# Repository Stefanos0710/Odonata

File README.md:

# Odonata

Odonata is an autonomous indoor drone controlled over a local network. I had the idea for the project, after I once bought a drone that broke after just two days because I struggled to control it manually. Sothat it doesn´t crash again, I decided to build a new,  autonomous drone and named it Odonata, after the Latin word for dragonfly.

The drone weighs about 300g and uses a 3S 11.1V 850mAh battery, giving it a flight time of roughly 5 minutes. With around 1100g of thrust, it achieves a 3:1 thrust-to-weight ratio, which allows precise flights. For navigation, it has 4 ToF (Time-of-Flight) sensors to track its position in the room, and it can perform controlled autonomous landings using a camera that detects AprilTags on the landing station. The landing station is designed with self-centering sticks, sothat even with a positioning error of about 1cm, the drone can still lands safely.

Odonata runs on a Raspberry Pi Zero 2W and a DarwinFPV flight controller, connected together via a custom PCB. With this setup the Pi can send and receive data using MAVLink commands (such as starting the motors, pitching, etc.). The project is split into two parts: the drone itself and a local server. The server hosts a web-based cockpit where you can monitor the drone, test the motors, and start-stop flights. Because it works locally, you can easily host the server on your laptop, PC, or a separate Raspberry Pi.

## First Flight

The first version of Odonata in flight:

[Watch in full quality on YouTube](https://www.youtube.com/shorts/tDMgUdCkJ7U)

## Zine Poster

Here is the Zine poster of my project Odonata:

## Website/Cockpit

Here you can see the user interface of the cockpit where you can monitor the drone and send commands:

## CAD Model

The CAD design of Odonata is split into several parts, like the arms, the walls, the base, the cover, and the propguards. Everything is attached using M2 screws and heat inserts, or slide-ins and snap-fits. The .step, .stl and f3d/f3z files can be found at the /CAD directory. Here are some nice renders of the assembled drone:

(All parts were modeled and rendered in Autodesk Fusion 360)

<details>
<summary><b>Click here to view more renders</b></summary>

</details>

## PCB

This custom PCB is designed in KiCad and makes the flawless communication between the Flight Controller and the Raspberry Pi Zero 2W possible, and also connects the servo, the ToF sensors and camera to a working system. It uses a 4-layer design for the optimal routing and to ensure no noise on the power lines.

### Schematics

### PCB-Layers

The PCB uses 4 layers: 1. TOP-Signal layer 2. GND layer 3. Power layer 4. Signal and GND layer

#### **1. Layer (Top-Signal)**

#### **2. Layer (GND)**

#### **3. Layer (Power)**

#### **4. Layer (Signal/GND)**

#### **PCB 3D-Rendering**

| Front | Back |
|----------|-------------|
|  |  |

#### JLCPCB Order

## How to build Odonata (Step-by-Step)

If you want to rebuild this drone without any modifications, you can follow these next steps. If you want to modify the drone, you can follow along the guide, you just have to adjust it to your changes:

### 1. Getting the parts

1. Download the whole repository on your computer by running these commands in your terminal to download the firmware, CAD, and PCB:

   ```bash
   git clone https://github.com/Stefanos0710/Odonata.git
   cd Odonata
   ```

   After that, you will have cloned the entire project onto your computer.

2. Next, you have to print out the 3D parts, and therefore you have 2 options, based on whether you have a 3D printer or not:
   1. If you have a 3D printer: upload the stl files from `/CAD/f3d_stl` into your slicer software. You have to print every file separately. So for the propguards you need 4, the motor arms you need 4, the base you need 1, the wall you need 1, the cover you need 1, and you need the camera holder. For the landing station, you need the catcher and the AprilTag holder.
   2. If you don't have a 3D printer, you can use a company like PCBWay, JLCPCB, or any other 3D printing service. There you have to upload the exact same files I mentioned previously and order them.
   3. Overall for the filament, if you can choose which one you can use, I would assume to use TPU for the propguards and print the rest with PETG for the best stability. For the color, if you like the style of the drone, it should be light/lime green and purple/blue.

3. Next, you should order the PCB. Therefore you need the gerber files which you find at `PCB/gerbers` as a `gerbers.zip` file. This file you can upload on a service like PCBWay, JLCPCB, or any other of your choice. Make sure to select 4 layers, and for the color it doesn't matter, but in this case I used the typical green one. Otherwise, I use the default options, so FR-4 as material.

4. Next, we need to get/buy the rest of the parts. A list with all parts you can find further down in the README, or in the `BOM.csv` file. There is the cost of the parts, the links, name, and description. INFO: the shipping cost is calculated for ordering to Bavaria, Germany, so it might change for you. But the rough price without shipping is 222,71€.

### 2. Setting up the Raspberry Pi Zero 2 W

After you got all the parts, we can start building the drone. And therefore we will start setting up the Raspberry Pi Zero 2 W:

1. Firstly, you need to download the Raspberry Pi Imager software on your computer, so that you can install the OS on the Raspberry Pi. First open this site https://www.raspberrypi.com/software/ and download it for your OS (Windows/macOS/Linux).
2. After downloading, you need to attach a micro SD card with at least 16GB to the computer, so that you can flash the OS and attach it later into the Raspberry Pi.
3. Then you choose the Raspberry Pi OS Lite, without the desktop, so that we don't waste resource power on that.
4. During that procedure, you will need to add the name (I assume to use "odonata" as the name), the WLAN (this must match the WLAN that you are connected to with your computer and later your server), and very important is to activate SSH, and lastly, you have to add a username and a password.
5. Then you detach the micro SD from your computer and attach it into the Raspberry Pi and connect it with a USB for power.
6. After waiting for about 5 min so that the OS can boot, you can type (for Windows):

   ```bash
   ssh yourusername@odonata.local
   ```

   And so you should be connected to the Raspberry Pi.
7. Now we update the system by typing in:

   ```bash
   sudo apt update
   sudo apt upgrade -y
   ```

8. After that, type in `sudo raspi-config` and activate the camera, the SPI, and the I2C.
9. After that, we have to install Python and Git. It's mostly already installed, but to update it's good:

   ```bash
   sudo apt install python3 python3-pip python3-venv git -y
   python3 --version
   pip3 --version
   git --version
   ```

   If you see no error, then everything is fine and installed.
10. And lastly, you have to copy the drone folder from firmware to the Raspberry Pi, and you can do it with this:

   ```bash
   git clone --depth 1 https://github.com/Stefanos0710/Odonata.git temp_repo
   mv temp_repo/firmware/drone ./drone
   mv temp_repo/firmware/requirements.txt ./
   rm -rf temp_repo

   cd drone
   pip install -r requirements.txt
   ```

11. Then, to activate the communication with the FC, you have to also add in `sudo raspi-config` under Interface Options -> Serial Port:
    - Login shell over serial? → No
    - Enable serial hardware? → Yes
    And then reboot.

### 3. Flight Controller Configuration

1. After we set up the Pi, we have to configure the FC (Flight Controller) so that we can use MAVLink on it. Therefore, you have to firstly install Mission Planner and then connect the FC with a USB cable to the PC.
2. Then you have to choose the COM port and the baud number that should be 115200, and then click Connect.
3. Then open the menu under Initial Setup and then Install Firmware, then select ArduCopter.
4. During that process, the firmware is installed and the FC is rebooted multiple times.
5. After that, you should read a text called ArduCopter Vx.x.x, and if Mission Planner connected again, then all is perfect.
6. Then we have to configure the parameters in Mission Planner. Therefore you go under Config to Full Parameter List and fill this out:
   - `SERIAL2_PROTOCOL = 2`
   - `SERIAL2_BAUD = 115`
7. This activates MAVLink2 which allows the communication with the Pi, and the baud number is the standard for drones with MAVLink. And after clicking on "Write Params", you are finished and you set everything up.

### 4. PCB Soldering

1. Now you have to solder all the SMD parts on the drone PCB. There isn't really a step-by-step for this, try to orientate yourself from the PCB renders, the schematics, and PCB layer 1.

### 5. Drone Assembly

After everything is soldered, you need to assemble the hardware parts:

1. Place the PCB on the base that was 3D printed, then add the placeholders (spacers) from the FC. Put the FC on it and screw it on with the M2 12mm screws.
2. Attach the Raspberry Pi to the male pins.
3. For the power, I firstly recommend to use a laboratory power supply so that you don't destroy your battery if something is wrong.
4. To connect everything, you need to connect the TX and RX cables from J2 with the RX and TX cables from the FC, and the rest of the parts are pretty easy to connect. Orientate yourself here again from the schematics and the PCB design.
5. Lastly run that command to install mavproxy:

   ```bash
   python3 mavproxy.py --master=/dev/serial0 --baudrate 115200 --aircraft MyCopter
   ```

6. And now we can attach the rest of the parts. Firstly, you have to insert the heat inserts with a soldering iron into the parts. Therefore you have to add them to the motor arms and the walls.
7. After that, you have to place the arms in the holding parts from the base and screw them with the M2 6mm screws into the base.
8. Next, you place the prop guards at the place where the motors go and screw them again with 6mm screws.
9. And now you have to lengthen the cables from the motors and place them in the cable canal from the arm into the inside of the drone, and solder the cables onto the FC pads for the motors.
10. Next, you have to attach the camera holder to the servo and also place the camera module into it, and place it in the front of the base. Make sure that the camera cable goes above the servo, connect the servo cable with its JST-GH cable, and attach it onto the PCB.
11. Next, solder the JST-GH cables to the ToF sensors and also add them to the PCB.
12. After all of this, you can place the walls and screw them on the base.
13. Next, place all the ToF sensors in their positions and make sure to press them in so that they hold their place. And now you are ready for the first test.

### 6. Server Setup

1. Go to your server computer or on the computer where you are currently working, and run these commands:

   ```bash
   git clone --depth 1 https://github.com/Stefanos0710/Odonata.git temp_repo
   mv temp_repo/firmware/server ./server
   mv temp_repo/firmware/requirements.txt ./
   rm -rf temp_repo

   cd server
   pip install -r requirements.txt

   fastapi dev
   ```

2. Then open `127.0.0.1:8000` and you will see the drone cockpit.
3. There you have to firstly add the IP by pressing "Connect Drone" or wait until the IP shows up, and connect the drone.
4. Then start the drone and test every motor and every component independently. If everything works fine, you are ready for the final step!

### 7. Final Touches

1. Now you can attach the propellers to the drone, and make sure they sit very tight.
2. After also attaching the battery and the on/off switch at the cover, you now have to print this paper out ([april_tag_print.pdf](images/april_tag_print.pdf)) and add it to the AprilTag holder.
3. Attach the AprilTag holder under the catcher, place the drone on the catcher, and let it start via the cockpit by pressing "Start Flight" and see the magic happen.

## BOM (Bill of Materials)

Here is a list of components and parts I used for this project:
(You can also find the csv file [here](BOM.csv))

| Name | Description | Link | Unit Cost (€) | Quantity | Price (€) | Shipping Cost | Total |
|---|---|---|---|---|---|---|---|
| C1 | 10uF 0805 Capacitor | [LCSC](https://www.lcsc.com/product-detail/C95841.html?s_z=n_q_t_Capacitors&spm=wm.fly.bg.6.xh___wm.ssy.tc.0.tz&lcsc_vid=Q1JYUFwDTgBYAVFWFVJbUwVfQ1BdVFFQRQBZXlEFE1MxVlNeR1FWVVFSQVNYUzsOAxUeFF5JWBYZEEoKFBINSQcJGk4NBhADEA4cHktXRlVaSQwSGg0%3D) | 0,03 | 10,00 | 0,34 | 18,91 | |
| C2, C3 | 150pF 0603 Capacitor | [LCSC](https://www.lcsc.com/product-detail/C37298.html?s_z=n_q_t_Capacitors&spm=wm.fly.bg.1.xh___wm.ssy.tc.0.tz&lcsc_vid=Q1JYUFwDTgBYAVFWFVJbUwVfQ1BdVFFQRQBZXlEFE1MxVlNeR1FWVVFSQVNYUzsOAxUeFF5JWBYZEEoKFBINSQcJGk4NBhADEA4cHktXRlVaSQwSGg0%3D) | 0,01 | 50,00 | 0,41 | 18,91 | |
| C4 | 22uF 0805 Capacitor | [LCSC](https://www.lcsc.com/product-detail/C602037.html?s_z=n_q_t_Capacitors&spm=wm.fly.bg.0.xh___wm.ssy.tc.0.tz&lcsc_vid=Q1JYUFwDTgBYAVFWFVJbUwVfQ1BdVFFQRQBZXlEFE1MxVlNeR1FWVVFSQVNYUzsOAxUeFF5JWBYZEEoKFBINSQcJGk4NBhADEA4cHktXRlVaSQwSGg0%3D) | 0,00 | 100,00 | 0,48 | 18,91 | |
| C5 | 1000uF Electrolytic Capacitors 10mm*5mm | [LCSC](https://www.lcsc.com/product-detail/C1579458.html?s_z=n_q_ESY108M010AH2EA%2520&spm=wm.fly.bg.0.xh&lcsc_vid=R1daUV0HFlVaAlIERwUNVlUATlNYBAdQQwNcVgFUQFgxVlNeR1FWUlRUR1RcUDsOAxUeFF5JWBYZEEoKFBINSQcJGk4dAgUUFAk%3D) | 0,15 | 1,00 | 0,15 | 18,91 | |
| C7 | 100nF 0603 Capacitor | [LCSC](https://www.lcsc.com/product-detail/C77058.html?s_z=s_c_Ceramic%2520Capacitors&spm=wm.fly.bg.26.xh&lcsc_vid=R1daUV0HFlVaAlIERwUNVlUATlNYBAdQQwNcVgFUQFgxVlNeR1FWUlZfQ1hfVzsOAxUeFF5JWBYZEEoKFBINSQcJGk4NBhADEA4cHktXRlVeSQwSGg0%3D) | 0,03 | 1,00 | 0,03 | 18,91 | |
| C8 | 100uF Electrolytic 6.3mm 11mm Capacitor | [LCSC](https://www.lcsc.com/product-detail/C135785.html?s_z=s_p_35PX100MEFC6.3X11&spm=wm.fly.bg.0.xh&lcsc_vid=R1daUV0HFlVaAlIERwUNVlUATlNYBAdQQwNcVgFUQFgxVlNeR1FWUl1TRVdaVjsOAxUeFF5JWBYZEEoKFBINSQcJGk4dAgUUFAk%3D) | 0,05 | 5,00 | 0,26 | 18,91 | |
| C9 | 100nF 0805 Capacitor | [LCSC](https://www.lcsc.com/product-detail/C1711.html?s_z=s_c_Ceramic%2520Capacitors&spm=wm.fly.bg.1.xh&lcsc_vid=R1daUV0HFlVaAlIERwUNVlUATlNYBAdQQwNcVgFUQFgxVlNeR1FWUVVQR1RZUjsOAxUeFF5JWBYZEEoKFBINSQcJGk4eFQsCAgIaSgADAwAHC0slRlJbUFxTWQkaCgg%3D) | 0,01 | 50,00 | 0,35 | 18,91 | |
| D2 | Schottky-Diode 3A | [LCSC](https://www.lcsc.com/product-detail/C7436556.html?s_z=n_q_B340%2520DO-214AB&spm=wm.fly.bg.1.xh&lcsc_vid=R1daUV0HFlVaAlIERwUNVlUATlNYBAdQQwNcVgFUQFgxVlNeR1FWUVBQQ1NXUDsOAxUeFF5JWBYZEEoKFBINSQcJGk4dAgUUFAk%3D) | 0,06 | 10,00 | 0,63 | 18,91 | |
| FB1 | Ferrite Bead 0805 300 ohm 2A | [LCSC](https://www.lcsc.com/product-detail/C67451.html?s_z=n_q_Ferrite%2520Bead%25200805%2520300%2520ohm%25202A&spm=wm.fly.bg.0.xh&lcsc_vid=R1daUV0HFlVaAlIERwUNVlUATlNYBAdQQwNcVgFUQFgxVlNeR1FWUVNVQlJWUDsOAxUeFF5JWBYZEEoKFBINSQcJGk4eFQsCAgIaSgADAwAHC0slQFVdUVFTQU8GEwkK) | 0,02 | 50,00 | 0,78 | 18,91 | |
| J1 | female connector with pi | [LCSC](https://www.lcsc.com/product-detail/C50980.html?s_z=n_q_p_Female%2520Header%25202.54mm%25202x20%2520vertical&spm=wm.ssy.bg.2.xh&lcsc_vid=R1daUV0HFlVaAlIERwUNVlUATlNYBAdQQwNcVgFUQFgxVlNeR1FWUV1QQ1ZcVzsOAxUeFF5JWBYZEEoKFBINSQcJGk4eFQsCAgIaSgADAwAHC0slQVZaUlVIHxUDCw%3D%3D) | 0,20 | 5,00 | 0,99 | 18,91 | |
| J2 | JST-GH 1x03-1MP_P1.25mm_Vertical | [LCSC](https://www.lcsc.com/product-detail/C161691.html?s_z=n_q_BM03B-GHS-TBT&spm=wm.fly.bg.0.xh&lcsc_vid=R1daUV0HFlVaAlIERwUNVlUATlNYBAdQQwNcVgFUQFgxVlNeR1FWUFdXRlNYUTsOAxUeFF5JWBYZEEoKFBINSQcJGk4eFQsCAgIaSgADAwAHC0slQlFXX1RIHxUDCw%3D%3D) | 0,67 | 1,00 | 0,67 | 18,91 | |
| J3 | JST-XH 1x04 | [LCSC](https://www.lcsc.com/product-detail/C144395.html?s_z=s_p_B4B-XH-A%28LF%29%28SN%29&spm=wm.fly.bg.2.xh&lcsc_vid=R1daUV0HFlVaAlIERwUNVlUATlNYBAdQQwNcVgFUQFgxVlNeR1FWUFBTQFlbXzsOAxUeFF5JWBYZEEoKFBINSQcJGk4dAgUUFAk%3D) | 0,05 | 10,00 | 0,48 | 18,91 | |
| J4 | JST-GH 1x03-1MP_P1.25mm_Horizontal | [LCSC](https://www.lcsc.com/product-detail/C514175.html?s_z=s_p_SM03B-GHS-TB%28LF%29%28SN%29&spm=wm.fly.bg.1.xh&lcsc_vid=R1daUV0HFlVaAlIERwUNVlUATlNYBAdQQwNcVgFUQFgxVlNeR1FWUFFRQFdXVTsOAxUeFF5JWBYZEEoKFBINSQcJGk4dAgUUFAk%3D) | 0,12 | 5,00 | 0,60 | 18,91 | |
| J5, J6 | XT30-Female Vertical | [LCSC](https://www.lcsc.com/product-detail/C19268023.html?s_z=n_q_Amass%2520XT30U%2520&spm=wm.fly.bg.3.xh&lcsc_vid=R1daUV0HFlVaAlIERwUNVlUATlNYBAdQQwNcVgFUQFgxVlNeR1FWUFxSQVNYXjsOAxUeFF5JWBYZEEoKFBINSQcJGk4dAgUUFAk%3D) | 0,21 | 5,00 | 1,06 | 18,91 | |
| J7 | JST-GH 1x02 vertical | [LCSC](https://www.lcsc.com/product-detail/C161690.html?s_z=n_q_BM02B-GHS-TBT&spm=wm.fly.bg.0.xh&lcsc_vid=R1daUV0HFlVaAlIERwUNVlUATlNYBAdQQwNcVgFUQFgxVlNeR1FWX1RQQlheUTsOAxUeFF5JWBYZEEoKFBINSQcJGk4eFQsCAgIaSgADAwAHC0slRlhcUVxWRVJADxALGw%3D%3D) | 0,18 | 5,00 | 0,91 | 18,91 | |
| J8, J9, J10 | JST-GH 1x05 Vertical | [LCSC](https://www.lcsc.com/product-detail/C189891.html?s_z=n_q_BM05B-GHS-TBT&spm=wm.fly.bg.0.xh&lcsc_vid=R1daUV0HFlVaAlIERwUNVlUATlNYBAdQQwNcVgFUQFgxVlNeR1FWX1VRRVRfUzsOAxUeFF5JWBYZEEoKFBINSQcJGk4eFQsCAgIaSgADAwAHC0slRldfUV1WWQkaCgg%3D) | 0,30 | 5,00 | 1,51 | 18,91 | |
| J11 | JST-GH 1x05 Horizontal | [LCSC](https://www.lcsc.com/product-detail/C189896.html?s_z=n_q_SM05B-GHS-TB) | 0,18 | 5,00 | 0,89 | 18,91 | |
| L1 | Inductor 7.3x7.3_4.5H 15uH 5A | [LCSC](https://www.lcsc.com/product-detail/C7461222.html?spm=wm.fly.bg.11.xh&lcsc_vid=QVFZAl1WRFhdX1wFRQNfXgFRTlRYVQdeRABaBl0CRFAxVlNeR1BcVFBQTlFcUTsOAxUeFF5JWBYZEEoKFBINSQcJGk4NBhADEA4cHktXRllfSQwSGg0%3D) | 0,88 | 1,00 | 0,88 | 18,91 | |
| Q1 | AOD4185 40V 40A | [LCSC](https://www.lcsc.com/product-detail/C5346822.html?s_z=n_q_AOD4185&spm=wm.fly.bg.1.xh&lcsc_vid=QVFZAl1WRFhdX1wFRQNfXgFRTlRYVQdeRABaBl0CRFAxVlNeR1BcU1ReR1JdVzsOAxUeFF5JWBYZEEoKFBINSQcJGk4eFQsCAgIaSgADAwAHC0slRVBYVl1QWQkaCgg%3D) | 0,16 | 5,00 | 0,81 | 18,91 | |
| R1, R11, R13, R15 | SMD Resistor 0603 10k 0.5% tolerance | [LCSC](https://www.lcsc.com/product-detail/C2930027.html?s_z=s_q_t_RESISTOR%252010K%25CE%25A9&spm=wm.fly.bg.1.xh___wm.ssy.tc.0.tz&lcsc_vid=QVFZAl1WRFhdX1wFRQNfXgFRTlRYVQdeRABaBl0CRFAxVlNeR1BcU1BfR1NYXjsOAxUeFF5JWBYZEEoKFBINSQcJGk4dAgUUFAk%3D) | 0,00 | 100,00 | 0,10 | 18,91 | |
| R2, R3 | 0603 4.7k 1% | [LCSC](https://www.lcsc.com/product-detail/C99782.html?s_z=n_q_t_0603%25204.7k%25201%2525&spm=wm.fly.bg.0.xh___wm.ssy.tc.0.tz&lcsc_vid=QVFZAl1WRFhdX1wFRQNfXgFRTlRYVQdeRABaBl0CRFAxVlNeR1BcUlRSQ1ZfUDsOAxUeFF5JWBYZEEoKFBINSQcJGk4eFQsCAgIaSgADAwAHC0slRVhdV1RUQE8GEwkK) | 0,00 | 100,00 | 0,14 | 18,91 | |
| R4, R6, R7, R10 | 0603 100k 1% | [LCSC](https://www.lcsc.com/product-detail/C2906980.html?s_z=n_q_t_0603%2520100k%25201%2525&spm=wm.fly.bg.1.xh___wm.ssy.tc.0.tz&lcsc_vid=QVFZAl1WRFhdX1wFRQNfXgFRTlRYVQdeRABaBl0CRFAxVlNeR1BcUlBXRFNYVzsOAxUeFF5JWBYZEEoKFBINSQcJGk4eFQsCAgIaSgADAwAHC0slTlhZX1ZIHxUDCw%3D%3D) | 0,00 | 100,00 | 0,11 | 18,91 | |
| R5 | 0603 24.9k 0,1 tolerance | [LCSC](https://www.lcsc.com/product-detail/C2654014.html?s_z=n_q_0603%252024.9k%25200.5%2525&spm=wm.fly.bg.1.xh&lcsc_vid=QVFZAl1WRFhdX1wFRQNfXgFRTlRYVQdeRABaBl0CRFAxVlNeR1BcUlJVRFReXjsOAxUeFF5JWBYZEEoKFBINSQcJGk4eFQsCAgIaSgADAwAHC0slRVheUV1eR08GEwkK) | 0,09 | 5,00 | 0,47 | 18,91 | |
| R8 | 0603 40.2k 1% | [LCSC](https://www.lcsc.com/product-detail/C12447.html?s_z=n_q_t_0603%252040.2k%25200%252C1%2525&spm=wm.fly.bg.1.xh___wm.ssy.tc.0.tz&lcsc_vid=QVFZAl1WRFhdX1wFRQNfXgFRTlRYVQdeRABaBl0CRFAxVlNeR1BcUlxWQVZeXjsOAxUeFF5JWBYZEEoKFBINSQcJGk4eFQsCAgIaSgADAwAHC0slRVdbU1RXQ08GEwkK) | 0,00 | 100,00 | 0,13 | 18,91 | |
| R9 | 0603 210k 1% | [LCSC](https://www.lcsc.com/product-detail/C54102584.html?s_z=n_q_t_210k%25200603&spm=wm.fly.bg.0.xh___wm.ssy.tc.0.tz&lcsc_vid=QVFZAl1WRFhdX1wFRQNfXgFRTlRYVQdeRABaBl0CRFAxVlNeR1BdUlVXT1FYXjsOAxUeFF5JWBYZEEoKFBINSQcJGk4dAgUUFAk%3D) | 0,0183 | 20 | 0,37 | 18,91 | |
| R12 | 0603 33k | [LCSC](https://www.lcsc.com/product-detail/C2075611.html?s_z=n_q_t_0603%252033k%25200.1%2525&spm=wm.fly.bg.1.xh___wm.ssy.tc.0.tz&lcsc_vid=QVFZAl1WRFhdX1wFRQNfXgFRTlRYVQdeRABaBl0CRFAxVlNeR1BcUl1TRFdZXjsOAxUeFF5JWBYZEEoKFBINSQcJGk4eFQsCAgIaSgADAwAHC0slRlNaU1NIHxUDCw%3D%3D) | 0,09 | 5,00 | 0,44 | 18,91 | |
| R14 | 0603 5.6k 0.1% | [LCSC](https://www.lcsc.com/product-detail/C445632.html?s_z=n_q_0603%25205.6k%25200.1%2525&spm=wm.fly.bg.1.xh&lcsc_vid=QVFZAl1WRFhdX1wFRQNfXgFRTlRYVQdeRABaBl0CRFAxVlNeR1BcUVVVQ1dfXjsOAxUeFF5JWBYZEEoKFBINSQcJGk4eFQsCAgIaSgADAwAHC0slRVFZUlJXRk8GEwkK) | 0,07 | 5,00 | 0,36 | 18,91 | |
| R16 | 0603 3.3k 1% | [LCSC](https://www.lcsc.com/product-detail/C2907023.html?s_z=n_q_t_3.3k%25200603&spm=wm.fly.bg.0.xh___wm.ssy.tc.0.tz&lcsc_vid=QVFZAl1WRFhdX1wFRQNfXgFRTlRYVQdeRABaBl0CRFAxVlNeR1BdU1xSQVFWVDsOAxUeFF5JWBYZEEoKFBINSQcJGk4eFQsCAgIaSgADAwAHC0slQ1dWUVxVWQkaCgg%3D) | 0,0011 | 100 | 0,11 | 18,91 | |
| U1 | TCA9548APWR | [LCSC](https://www.lcsc.com/product-detail/C130026.html?s_z=n_q_TCA9548APWR&spm=wm.fly.bg.0.xh&lcsc_vid=QVFZAl1WRFhdX1wFRQNfXgFRTlRYVQdeRABaBl0CRFAxVlNeR1BcUVBXR1leUTsOAxUeFF5JWBYZEEoKFBINSQcJGk4eFQsCAgIaSgADAwAHC0slQ1VbUVdUWQkaCgg%3D) | 0,57 | 1,00 | 0,57 | 18,91 | |
| U2 | mp1584en | [LiD/Aliexpress](https://de.aliexpress.com/item/1005007196431727.html?spm=a2g0o.productlist.main.8.5489RptfRptfDv&algo_pvid=5360c05b-13d8-4095-b5fc-a3890fa62c09&algo_exp_id=5360c05b-13d8-4095-b5fc-a3890fa62c09-7&pdp_ext_f=%7B%22order%22%3A%2288%22%2C%22eval%22%3A%221%22%2C%22fromPage%22%3A%22search%22%7D&pdp_npi=6%40dis%21EUR%214.58%210.99%21%21%2135.24%217.59%21%40211b655217801340919082663e8280%2112000039768133547%21sea%21DE%210%21ABX%211%210%21n_tag%3A-29910%3Bd%3A3d5500f9%3Bm03_new_user%3A-29895%3BpisId%3A5000000204872307&curPageLogUid=jxjSNTFxpzz5&utparam-url=scene%3Asearch%7Cquery_from%3A%7Cx_object_id%3A1005007196431727%7C_p_origin_prod%3A#nav-specification) | 4,58 | 1,00 | 4,58 | 0 | |
| U3 | ADS1115 | [LCSC](https://www.lcsc.com/product-detail/C468683.html?s_z=n_q_t_ADS1115&spm=wm.fly.bg.2.xh___wm.ssy.tc.0.tz&lcsc_vid=QVFZAl1WRFhdX1wFRQNfXgFRTlRYVQdeRABaBl0CRFAxVlNeR1BdU1FTTllfUjsOAxUeFF5JWBYZEEoKFBINSQcJGk4NBhADEA4cHktfRFNADxALGw%3D%3D) | 1,43 | 1,00 | 1,43 | 18,91 | |
| JST GH 1.25 Set | JST GH1.25 GH 1.25mm Connector Kit 2/3/4/5/6/7/8/9/10Pin Housing Pre-Crimped Cable Wire | [Aliexpress](https://de.aliexpress.com/item/1005009363803762.html) | 17,79 | 1,00 | 17,79 | 0 | |
| XT30-F cable | XT30U Amass 1PCS Male Female Connector Plug With 16 AWG | [Aliexpress](https://de.aliexpress.com/item/1005006871265256.html) | 4,73 | 1,00 | 4,73 | 0 | |
| Cable | 2 Pins Super Soft Black Red Silicone Cable | [Aliexpress](https://de.aliexpress.com/item/1005006762917521.html) | 1,08 | 1,00 | 1,08 | 0 | |
| Flight Controller | DarwinFPV F411 15A AIO (FC+ESC+RX) ELRS | [Rotorama](https://www.rotorama.de/product/darwinfpv-f411-15a-aio-fc-esc-rx-elrs) | 53,39 | 1,00 | 53,39 | 0 | |
| Motors | Happymodel EX1204 5000KV 3S 3" Motor | [Aliexpress](https://de.aliexpress.com/item/1005003283337242.html#nav-review) | 37,79 | 1,00 | 37,79 | 0 | |
| Props | Gemfan Hurricane 3016 3inch Toothpick 3X1.6X3 3-Blade PC Propeller | [Aliexpress](https://de.aliexpress.com/item/1005003324572840.html) | 7,89 | 1,00 | 7,89 | 0 | |
| Battery | Tattu 3S Lipo Battery 850 mAh 11.1 V 150C 3S1P | [Amazon](https://www.amazon.de/TATTU-850mAh-Battery-Stecker-Drohnen/dp/B0CXDKXJLP) | 23,99 | 1,00 | 23,99 | 0 | |
| Raspberry Pi Zero 2 W | Raspberry Pi Zero 2 W | [Pi-Shop](https://www.pi-shop.ch/raspberry-pi-zero-2-w) | 19,53 | 1,00 | 19,53 | 13,5 | |
| Camera | 130° 8MP Camera | [Aliexpress](https://de.aliexpress.com/item/1005007274396582.html#nav-review) | 8,11 | 1,00 | 8,11 | 0 | |
| ToF Sensor | VL53L0X Time-of-Flight (ToF) Laser Ranging Sensor Breakout 940nm | [Aliexpress](https://de.aliexpress.com/item/1005008557812009.html) | 3,24 | 4,00 | 12,96 | 0 | |
| PCB | 4 Layer custom PCB | [JLCPCB](https://cart.jlcpcb.com/quote?stencilLayer=4&stencilWidth=100&stencilLength=100&stencilCounts=5&plateType=1&spm=Jlcpcb.Homepage.1010) | 5,99 | 1,00 | 5,99 | 7,81 | |
| Raspberry Pi Pin Header | BOOMELE(Boom Precision Elec) 2.54-2*20P | [LCSC](https://www.lcsc.com/product-detail/Female-Headers_BOOMELE-Boom-Precision-Elec-C50982_C50982.html) | 0,26 | 5,00 | 1,29 | 18,91 | |
| Screw 6mm | 50pcs Black 304 Stainless Steel Cross Phillips CM M2 6mm | [Aliexpress](https://de.aliexpress.com/item/1005005618746295.html) | 2,00 | 1,00 | 2,00 | 0 | |
| Screw 12mm | 50pcs Black 304 Stainless Steel Cross Phillips CM M2 12mm | [Aliexpress](https://de.aliexpress.com/item/1005005618746295.html) | 2,52 | 1,00 | 2,52 | 0 | |
| Heat insert | 50pcs M2 2mm | [Aliexpress](https://de.aliexpress.com/item/1005008318533389.html) | 2,66 | 1,00 | 2,66 | 0 | |
| Switch | KCD1 15*21mm 2 Pin Boat Switch | [Aliexpress](https://de.aliexpress.com/item/1005007987928702.html) | 0,38 | 5,00 | 1,90 | 18,91 | |
| Servo | SG90 | [Aliexpress](https://de.aliexpress.com/item/1005008107550639.html) | 1,91 | 1,00 | 1,91 | 0 | |
| **Sum Costs** |  |  |  |  | **224,62** | **40,22** | **264,84** |

Huge thanks to Fallout from Hack Club for inspiring me to build this project and for financing it!

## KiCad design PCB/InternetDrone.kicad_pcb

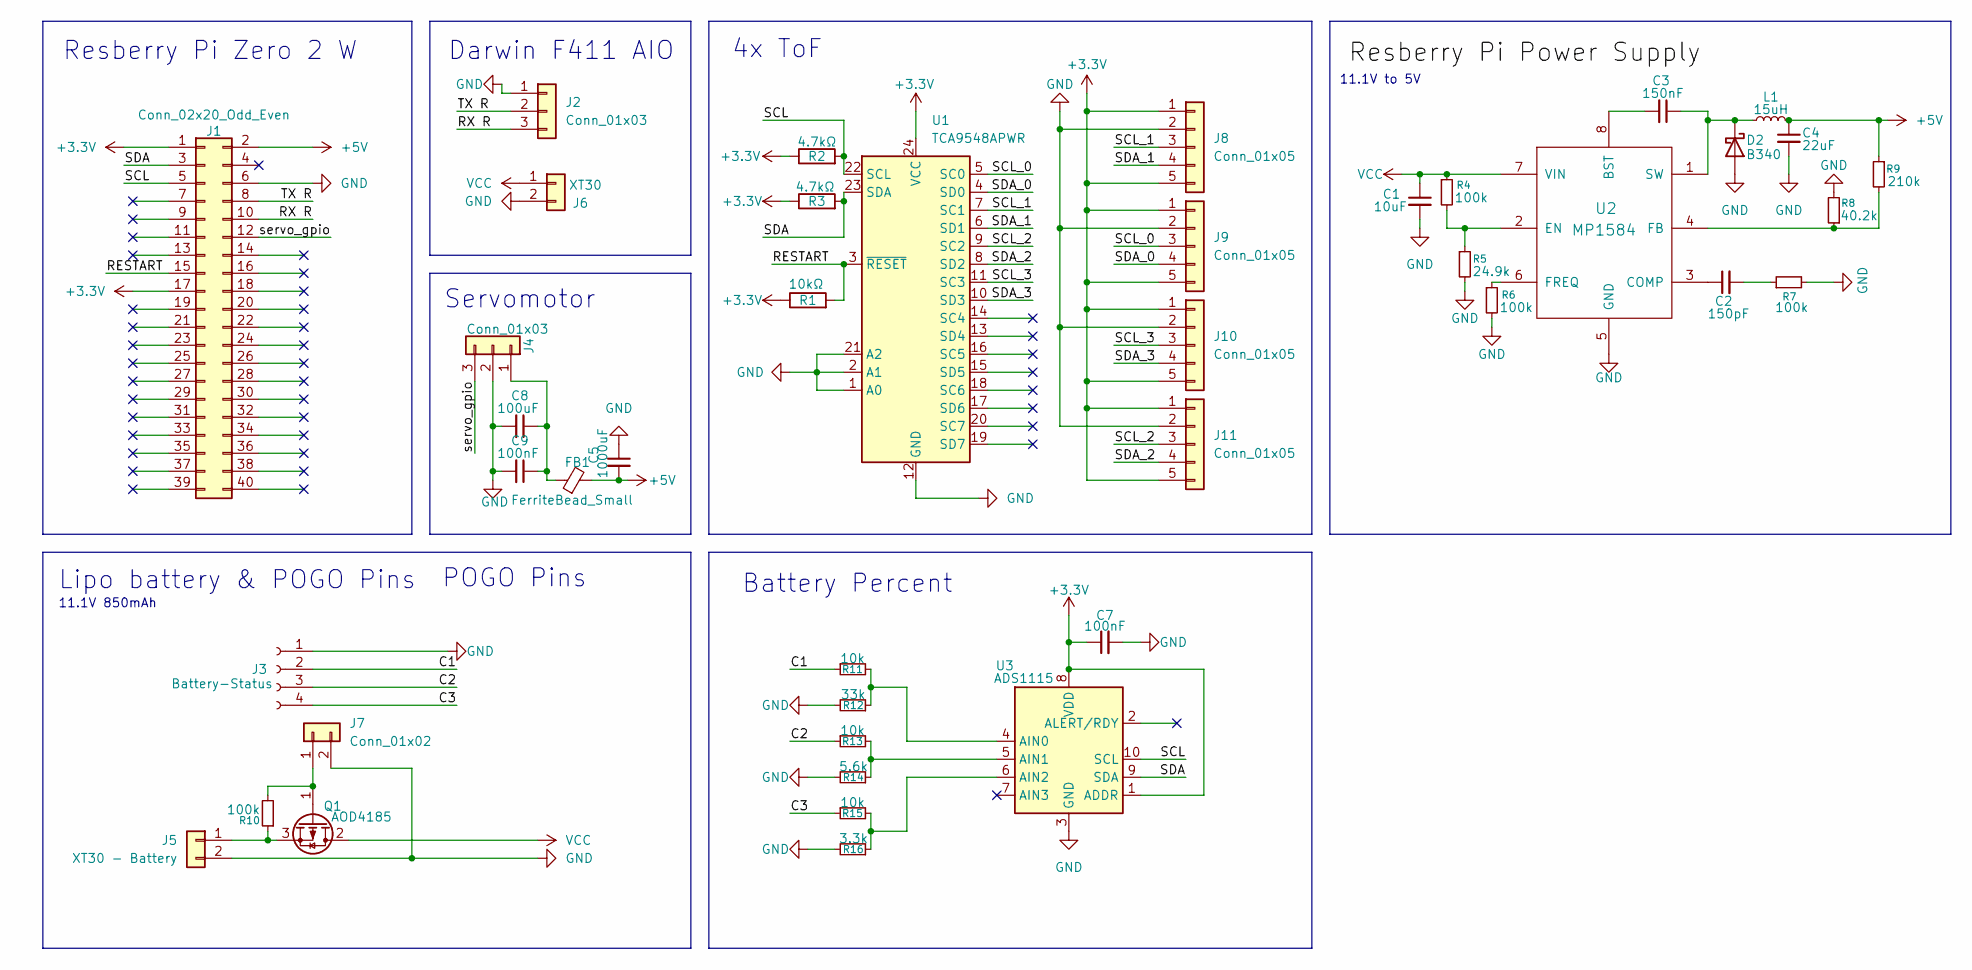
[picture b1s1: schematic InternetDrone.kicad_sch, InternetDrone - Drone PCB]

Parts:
C1: 10uF; C_0805_2012Metric
C2: 150pF; C_0603_1608Metric
C3: 150nF; C_0603_1608Metric
C4: 22uF; C_0805_2012Metric
C5: 1000uF; CP_Radial_D10.0mm_P5.00mm
C7: 100nF; C_0603_1608Metric
C8: 100uF; CP_Radial_D6.3mm_P2.50mm
C9: 100nF; C_0805_2012Metric
D2: B340; D_SMC
FB1: FerriteBead_Small; L_0805_2012Metric
J1: Conn_02x20_Odd_Even; PinHeader_2x20_P2.54mm_Vertical
J2: Conn_01x03; JST_GH_BM03B-GHS-TBT_1x03-1MP_P1.25mm_Vertical
J3: Battery-Status; JST_XH_B4B-XH-A_1x04_P2.50mm_Vertical
J4: Conn_01x03; JST_GH_SM03B-GHS-TB_1x03-1MP_P1.25mm_Horizontal
J5: XT30 - Battery; AMASS_XT30U-M_1x02_P5.0mm_Vertical
J6: XT30; AMASS_XT30U-M_1x02_P5.0mm_Vertical
J7: Conn_01x02; JST_GH_BM02B-GHS-TBT_1x02-1MP_P1.25mm_Vertical
J8, J9, J10: Conn_01x05; JST_GH_BM05B-GHS-TBT_1x05-1MP_P1.25mm_Vertical
J11: Conn_01x05; JST_GH_SM05B-GHS-TB_1x05-1MP_P1.25mm_Horizontal
L1: 15uH; L_7.3x7.3_H4.5
Q1: AOD4185; TO-252-2
R1: 10kΩ; R_0603_1608Metric
R2, R3: 4.7kΩ; R_0603_1608Metric
R4, R6, R7, R10: 100k; R_0603_1608Metric
R5: 24.9k; R_0603_1608Metric
R8: 40.2k; R_0603_1608Metric
R9: 210k; R_0603_1608Metric
R11, R13, R15: 10k; R_0603_1608Metric
R12: 33k; R_0603_1608Metric
R14: 5.6k; R_0603_1608Metric
R16: 3.3k; R_0603_1608Metric
U1: TCA9548APWR; TSSOP-24_4.4x7.8mm_P0.65mm
U2: MP1584; SOIC-8_3.9x4.9mm_P1.27mm
U3: ADS1115; TSSOP-10_3x3mm_P0.5mm

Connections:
+3.3V: C7.1, J1.1, J1.17, J8.1, J8.5, J9.1, J9.5, J10.1, J10.5, J11.1, J11.5, R1.1, R2.1, R3.1, U1.24 (VCC), U3.1 (ADDR), U3.8 (VDD)
+5V: C4.1, C5.2, FB1.2, J1.2, L1.2, R9.1
/C1: J3.2, R11.1
/C2: J3.3, R13.1
/C3: J3.4, R15.1
/RESTART: J1.15, R1.2, U1.3 (~RESET)
/RX R: J1.10, J2.3
/SCL: J1.5, R2.2, U1.22 (SCL), U3.10 (SCL)
/SCL_0: J9.3, U1.5 (SC0)
/SCL_1: J8.3, U1.7 (SC1)
/SCL_2: J11.3, U1.9 (SC2)
/SCL_3: J10.3, U1.11 (SC3)
/SDA: J1.3, R3.2, U1.23 (SDA), U3.9 (SDA)
/SDA_0: J9.4, U1.4 (SD0)
/SDA_1: J8.4, U1.6 (SD1)
/SDA_2: J11.4, U1.8 (SD2)
/SDA_3: J10.4, U1.10 (SD3)
/TX R: J1.8, J2.2
/servo_gpio: J1.12, J4.3
GND: C1.2, C4.2, C5.1, C7.2, C8.2, C9.2, D2.2 (A), J1.6, J2.1, J3.1, J4.2, J5.2, J6.2, J7.2, J8.2, J9.2, J10.2, J11.2, R5.2, R6.2, R7.2, R8.2, R12.2, R14.2, R16.2, U1.1 (A0), U1.2 (A1), U1.12 (GND), U1.21 (A2), U2.5 (GND), U3.3 (GND); also elsewhere on the board
unnamed: C2.2, R7.1
unnamed: C3.1, D2.1 (K), L1.1, U2.1 (SW)
unnamed: J5.1, Q1.3 (S), R10.1
unnamed: J7.1, Q1.1 (G), R10.2
unnamed: C3.2, U2.8 (BST)
unnamed: C2.1, U2.3 (COMP)
unnamed: R4.2, R5.1, U2.2 (EN)
unnamed: R8.1, R9.2, U2.4 (FB)
unnamed: R6.1, U2.6 (FREQ)
unnamed: R11.2, R12.1, U3.4 (AIN0)
unnamed: R13.2, R14.1, U3.5 (AIN1)
unnamed: R15.2, R16.1, U3.6 (AIN2)

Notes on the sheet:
POGO Pins
11.1V 850mAh
Battery Percent
11.1V to 5V
Resberry Pi Zero 2 W
Lipo battery & POGO Pins
Darwin F411 AIO
4x ToF
Servomotor

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
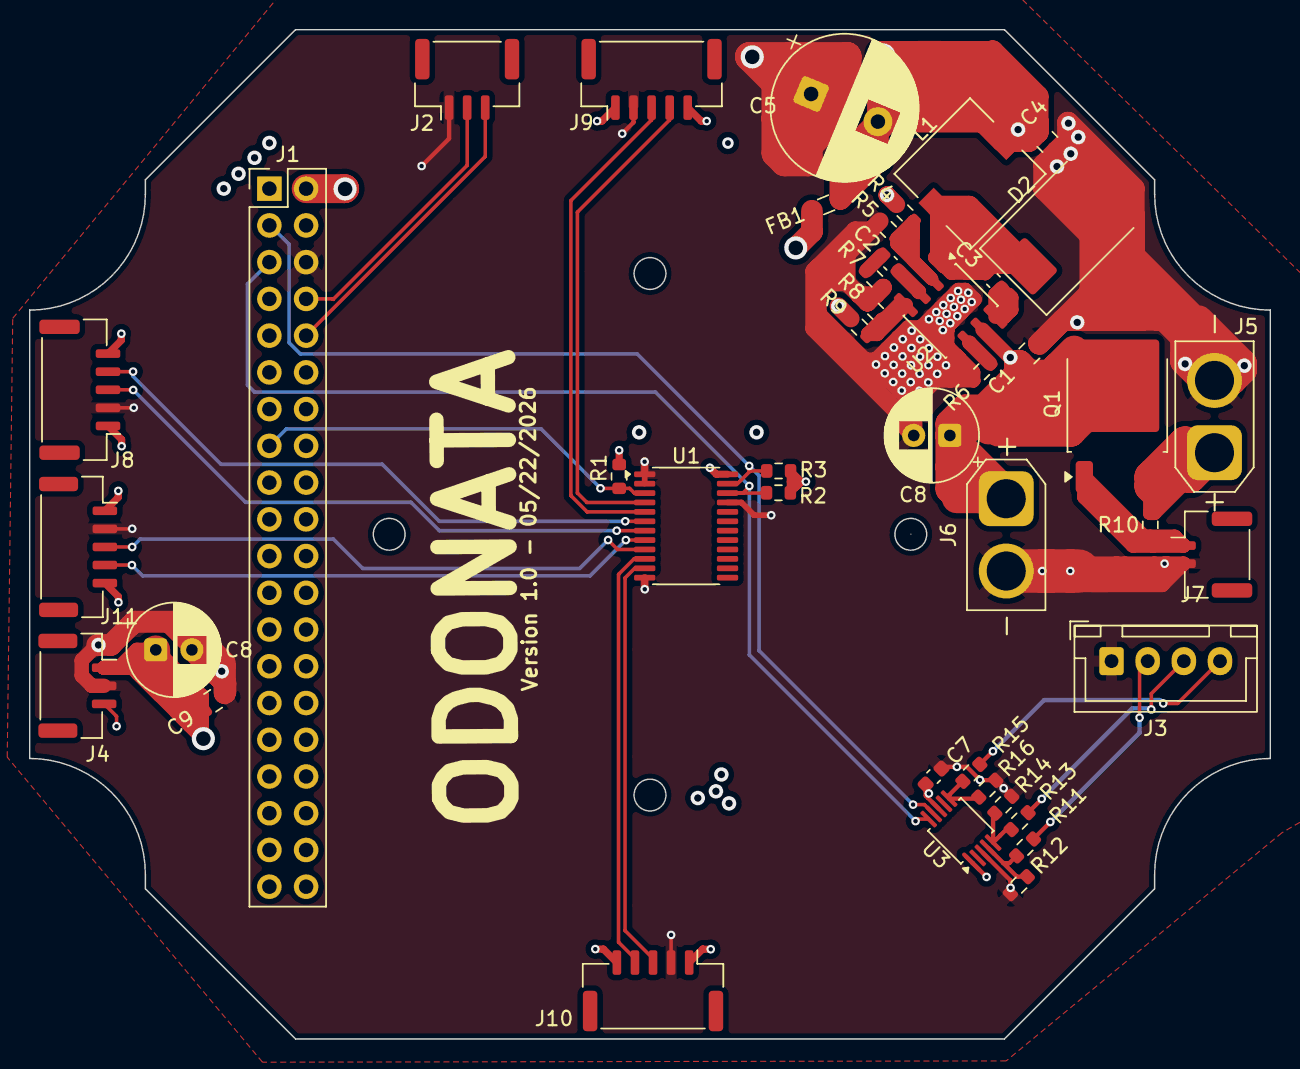
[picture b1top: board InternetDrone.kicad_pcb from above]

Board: 4 copper layers, 85.8 x 69.8 mm, 43 parts (0 on the bottom side), 34 nets.

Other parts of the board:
C8#2: 100uF; CP_Radial_D6.3mm_P2.50mm

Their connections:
GND: C8#2.2; also elsewhere on the board

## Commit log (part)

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2026-05-25 Add README file for firmware documentation
2026-05-25 Add main and motor scripts for drone firmware
2026-05-25 Refactor drone control logic and add motor activation function
2026-05-25 Add ToF sensor measurement functionality
2026-05-25 Refactor ToFSensor class to encapsulate setup and measurement logic
2026-05-25 Add threading support to ToFSensor for distance measurement loop
2026-05-25 Refactor ToFSensor class to improve distance measurement handling and add get_distances method
2026-05-25 Add initial requirements file for drone libraries
2026-05-25 Refactor ToFSensor class to manage running state and improve distance measurement loop
2026-05-25 Refactor motor and ToFSensor classes to improve motor arming logic and enhance distance measurement handling
2026-05-25 Refactor main and motor modules to improve code structure and enhance takeoff logic
2026-05-26 Refactor takeoff function to remove unused altitude measurement and add placeholder for yaw_drone function
2026-05-26 Update README and requirements; add camera module for Raspberry Pi
2026-05-26 Add camera setup and AprilTag detection functionality
2026-05-26 Enhance camera module with multi-threaded AprilTag detection and configurable parameters
2026-05-26 Fix camera index in VideoCapture and add servo control functionality
2026-05-26 Add battery status monitoring functionality
2026-05-27 Refactor battery status class and implement battery percentage calculation
2026-05-27 Fix battery percentage initialization and update voltage factor comment
2026-05-27 Add README file for drone firmware documentation
2026-05-27 Add docstrings for camera, motor, and servo functions to improve code documentation
2026-05-27 Enhance move_drone function with obstacle detection and no GPS mode support
2026-05-27 Enhance move_drone function with velocity initialization, obstacle avoidance, and hover mode support
2026-05-27 Add yaw_drone function for controlled yaw movement and enhance move_drone collision avoidance
2026-05-27 Enhance yaw_drone function to include duration parameter for controlled yaw movement
2026-05-27 Implement land_drone function for controlled landing using camera and distance sensor data
2026-05-27 Refactor flight control logic and update land_drone function for improved landing speed
2026-05-27 Refactor flight control functions and enhance modularity by adding battery status, servo movement, and distance sensor functions
2026-05-27 Add frontend files including HTML, CSS, and JavaScript for drone cockpit interface
2026-05-27 Revamp frontend layout and styling for Odonata cockpit with new HTML structure, CSS dark theme, and enhanced JavaScript functionality for video streaming and motor controls
2026-05-27 Refactor cockpit layout and styling for improved user interface, including updated header structure, action buttons, and dashboard organization
2026-05-27 Add drone connection and command classes to main.py for improved API functionality
2026-05-28 Refactor main.py to enhance API telemetry functionality and improve code organization
2026-05-28 Implement API commands for drone control, including start, stop, flight initiation, servo movement, and motor testing with error handling
2026-05-28 Add API endpoints for drone control and telemetry, including start, stop, servo movement, and motor testing
2026-05-28 Add frontend JavaScript and CSS for cockpit interface, including video stream and motor controls
2026-05-28 Add drone connection modal and API for managing connected IPs
2026-05-28 Implement WebRTC video streaming functionality and update frontend to support video display
2026-05-28 Add gerber files for PCB layout in zip format
2026-05-29 Adding the CAD files
2026-05-29 Add LFS CAD files
2026-05-29 add cad
2026-05-29 Move CAD files to LFS only
2026-05-29 adding the zine-poster!!!!
2026-05-29 adding the journal and some pictures
2026-05-30 Add drone assembly CAD file to LFS
2026-05-30 add BOM.csv
2026-05-30 Update BOM.csv and README.md with additional components and detailed project description; add firmware documentation and new images for the Odonata project.
2026-05-30 Add JLCPCB order image to README.md
2026-05-30 moved JLCPCB img
2026-05-30 Refactor README.md for clarity and conciseness; improve project description and technical details.
2026-05-30 Update README.md with step-by-step build instructions and add new components to BOM; include AprilTag print PDF
